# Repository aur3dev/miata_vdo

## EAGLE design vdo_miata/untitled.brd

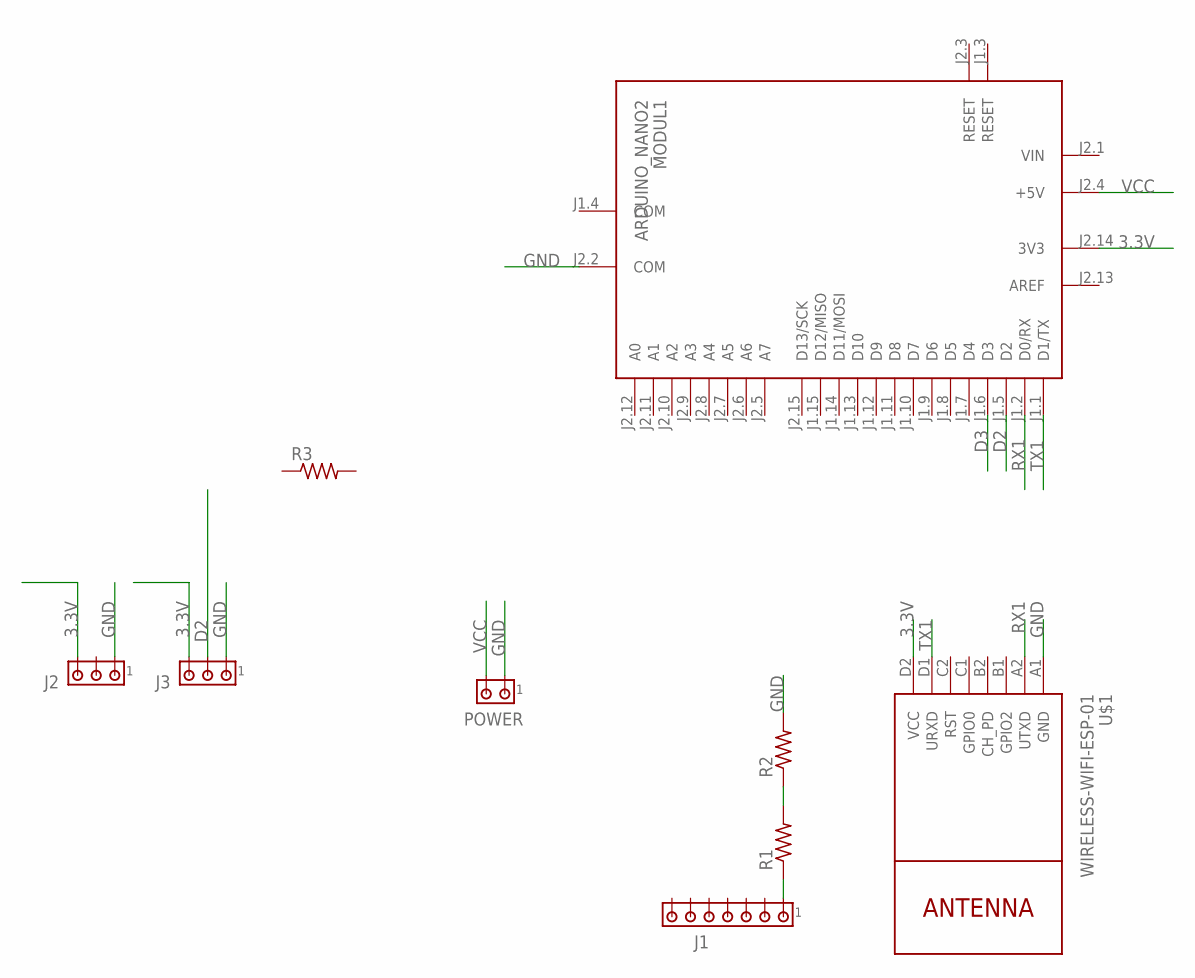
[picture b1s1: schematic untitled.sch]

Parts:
J1: MTA07-100; 10X07MTA
J2, J3: MTA03-100; 10X03MTA
MODUL1: ARDUINO_NANO2
POWER: MTA02-100; 10X02MTA
R1, R2, R3: R-US_0207/9; 0207/9
U$1: WIRELESS-WIFI-ESP-01

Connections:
3.3V: J2.3, J3.3, MODUL1.J2.14 (3V3), U$1.D2 (VCC)
AREF: MODUL1.J2.13 (AREF)
COM: MODUL1.J1.4 (COM)
D2: J3.2, MODUL1.J1.5 (D2)
D3: MODUL1.J1.6 (D3)
GND: J2.1, J3.1, MODUL1.J2.2 (COM), POWER.1, R2.2, U$1.A1 (GND)
unnamed: R1.2, R2.1
unnamed: J1.1, R1.1
RX1: MODUL1.J1.2 (D0/RX), U$1.A2 (UTXD)
TX1: MODUL1.J1.1 (D1/TX), U$1.D1 (URXD)
VCC: MODUL1.J2.4 (+5V), POWER.2
VIN: MODUL1.J2.1 (VIN)

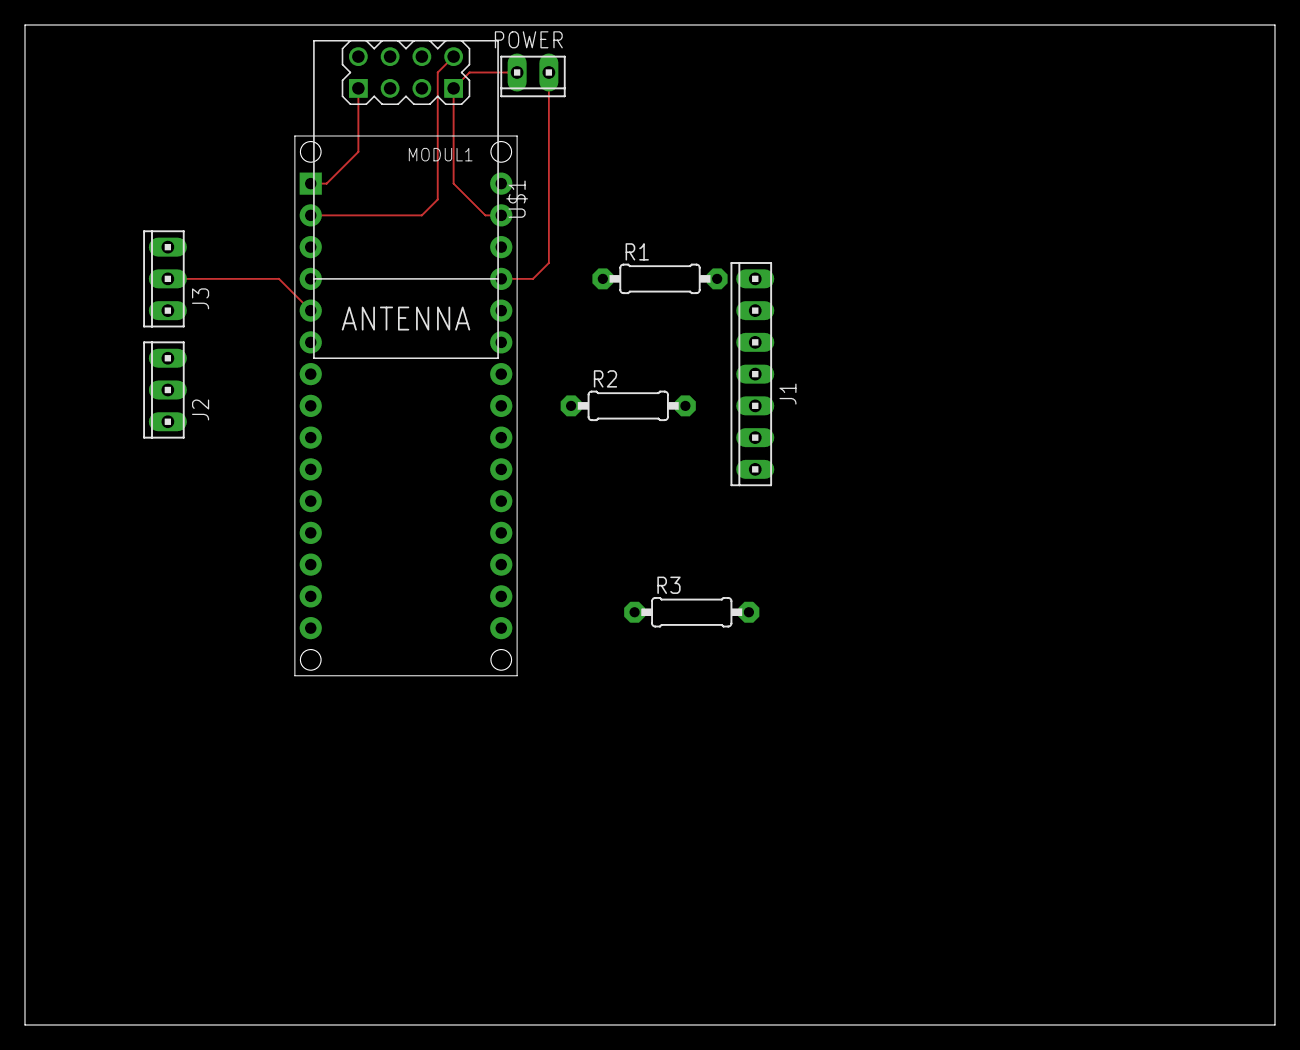
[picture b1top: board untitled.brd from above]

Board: 2 copper layers, 100.0 x 80.0 mm, 9 parts (0 on the bottom side), 8 nets.

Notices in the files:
parts and their libraries:
diy-modules: Released under the Creative Commons Attribution 4.0 International License: http://creativecommons.org/licenses/by/4.0
